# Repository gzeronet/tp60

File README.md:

# TP60

Custom PCB for gh60-like keyboard with trackpoint. Teensy 2.0 as main Controller.

Also see:

https://github.com/gzeronet/teensy-trackpoint-tmk-keyboard/

## PCB View

### Front

### Back

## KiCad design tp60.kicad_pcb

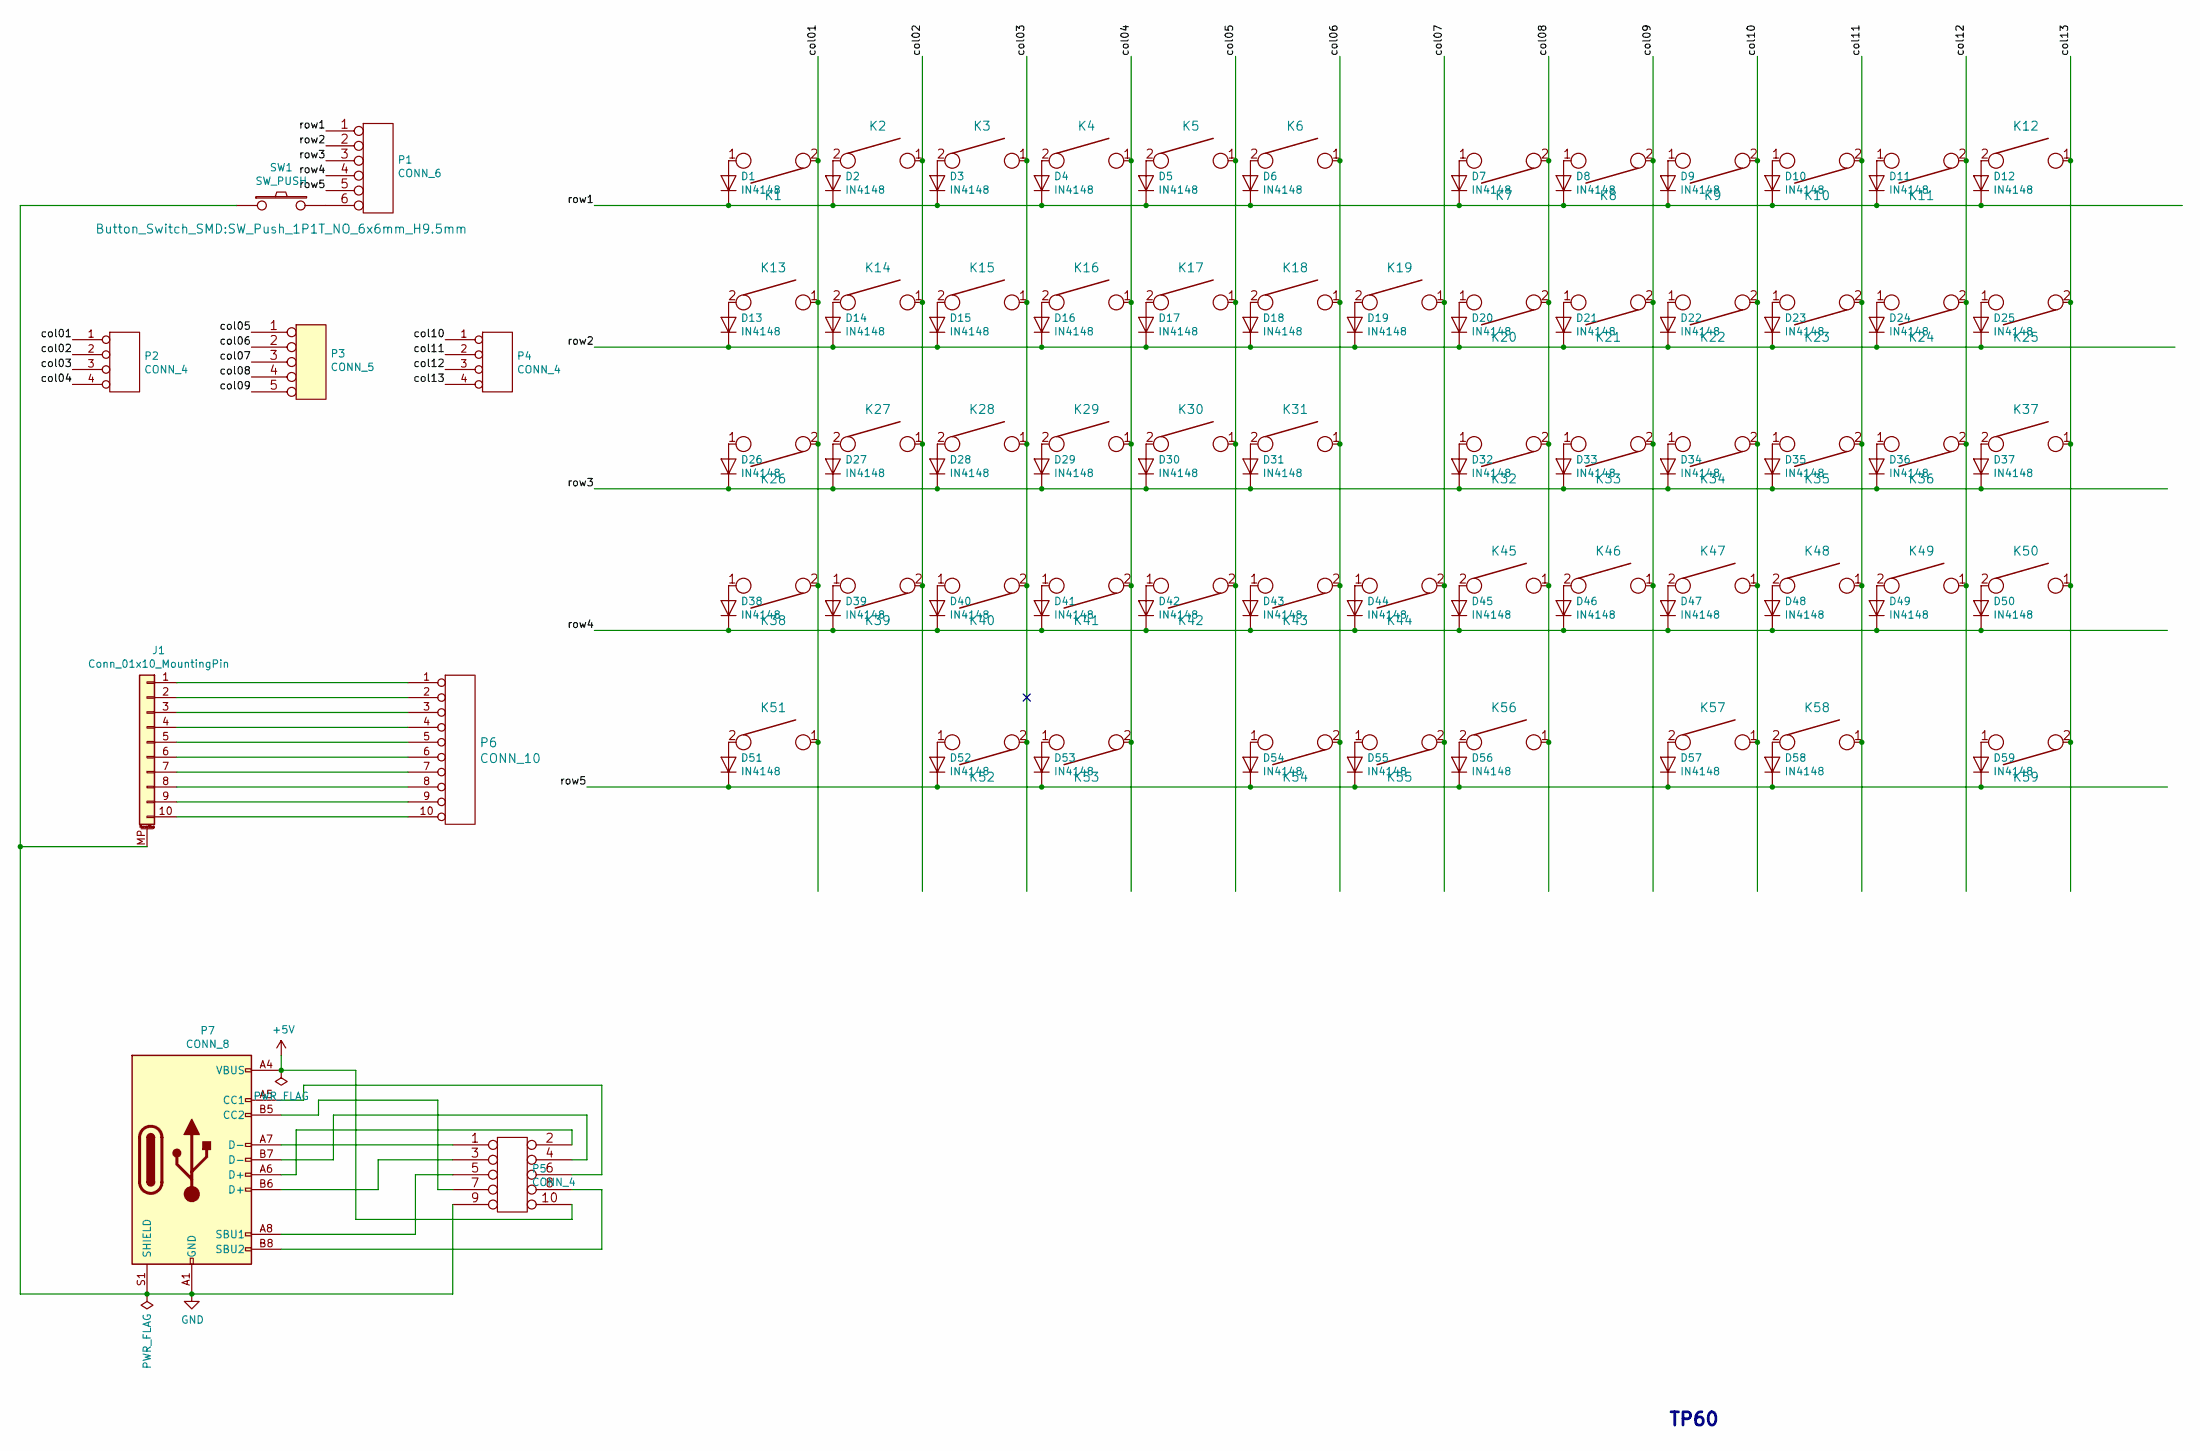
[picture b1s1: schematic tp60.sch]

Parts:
D1, D2, D3, D4, D5, D6, D7, D8, D9, D10, D11, D12, D13, D14, D15, D16, D17, D18, D19, D20, D21, D22, D23, D24, D25, D26, D27, D28, D29, D30, D31, D32, D33, D34, D35, D36, D37, D38, D39, D40, D41, D42, D43, D44, D45, D46, D47, D48, D49, D50, D51, D52, D53, D54, D55, D56, D57, D58, D59: IN4148; D_DO-35_SOD27_P7.62mm_Horizontal
J1: Conn_01x10_MountingPin; TE_1-84952-0_1x10-1MP_P1.0mm_Horizontal
K1, K2, K3, K4, K5, K6, K7, K8, K9, K10, K11, K12, K13, K14, K15, K16, K17, K18, K19, K20, K21, K22, K23, K24, K25, K26, K27, K28, K29, K30, K31, K32, K33, K34, K35, K36, K37, K38, K39, K40, K41, K42, K43, K44, K45, K46, K47, K48, K49, K50, K51, K52, K53, K54, K55, K56, K57, K58, K59: KEYSW; SW_MX_1280
P1: CONN_6; PinHeader_1x06_P2.54mm_Vertical
P2, P4: CONN_4; PinHeader_1x04_P2.54mm_Vertical
P3: CONN_5; PinHeader_1x05_P2.54mm_Vertical
P5: CONN_4; PinHeader_2x05_P2.54mm_Vertical
P6: CONN_10; PinHeader_2x05_P2.54mm_Vertical
P7: CONN_8; HRO-TYPE-C-31-M-12-PIN
SW1: SW_PUSH; SW_Push_1P1T_NO_6x6mm_H9.5mm

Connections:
+5V: P5.10, P7.A4 (VBUS), P7.A9 (VBUS), P7.B4 (VBUS), P7.B9 (VBUS)
/col01: K1.2, K13.1, K26.2, K38.2, K51.1, P2.1
/col02: K2.1, K14.1, K27.1, K39.2, P2.2
/col03: K3.1, K15.1, K28.1, K40.2, K52.2, P2.3
/col04: K4.1, K16.1, K29.1, K41.2, K53.2, P2.4
/col05: K5.1, K17.1, K30.1, K42.2, P3.1
/col06: K6.1, K18.1, K31.1, K43.2, K54.2, P3.2
/col07: K19.1, K44.2, K55.2, P3.3
/col08: K7.2, K20.2, K32.2, K45.1, K56.1, P3.4
/col09: K8.2, K21.2, K33.2, K46.1, P3.5
/col10: K9.2, K22.2, K34.2, K47.1, K57.1, P4.1
/col11: K10.2, K23.2, K35.2, K48.1, K58.1, P4.2
/col12: K11.2, K24.2, K36.2, K49.1, P4.3
/col13: K12.1, K25.2, K37.1, K50.1, K59.2, P4.4
/row1: D1.1 (K), D2.1 (K), D3.1 (K), D4.1 (K), D5.1 (K), D6.1 (K), D7.1 (K), D8.1 (K), D9.1 (K), D10.1 (K), D11.1 (K), D12.1 (K), P1.1
/row2: D13.1 (K), D14.1 (K), D15.1 (K), D16.1 (K), D17.1 (K), D18.1 (K), D19.1 (K), D20.1 (K), D21.1 (K), D22.1 (K), D23.1 (K), D24.1 (K), D25.1 (K), P1.2
/row3: D26.1 (K), D27.1 (K), D28.1 (K), D29.1 (K), D30.1 (K), D31.1 (K), D32.1 (K), D33.1 (K), D34.1 (K), D35.1 (K), D36.1 (K), D37.1 (K), P1.3
/row4: D38.1 (K), D39.1 (K), D40.1 (K), D41.1 (K), D42.1 (K), D43.1 (K), D44.1 (K), D45.1 (K), D46.1 (K), D47.1 (K), D48.1 (K), D49.1 (K), D50.1 (K), P1.4
/row5: D51.1 (K), D52.1 (K), D53.1 (K), D54.1 (K), D55.1 (K), D56.1 (K), D57.1 (K), D58.1 (K), D59.1 (K), P1.5
GND: J1.MP (MountPin), P5.9, P7.A1 (GND), P7.A12 (GND), P7.B1 (GND), P7.B12 (GND), P7.S1 (SHIELD), SW1.1
unnamed: D1.2 (A), K1.1
unnamed: D2.2 (A), K2.2
unnamed: D3.2 (A), K3.2
unnamed: D4.2 (A), K4.2
unnamed: D5.2 (A), K5.2
unnamed: D6.2 (A), K6.2
unnamed: D7.2 (A), K7.1
unnamed: D8.2 (A), K8.1
unnamed: D9.2 (A), K9.1
unnamed: D10.2 (A), K10.1
unnamed: D11.2 (A), K11.1
unnamed: D12.2 (A), K12.2
unnamed: D13.2 (A), K13.2
unnamed: D14.2 (A), K14.2
unnamed: D15.2 (A), K15.2
unnamed: D16.2 (A), K16.2
unnamed: D17.2 (A), K17.2
unnamed: D18.2 (A), K18.2
unnamed: D19.2 (A), K19.2
unnamed: D20.2 (A), K20.1
unnamed: D21.2 (A), K21.1
unnamed: D22.2 (A), K22.1
unnamed: D23.2 (A), K23.1
unnamed: D24.2 (A), K24.1
unnamed: D25.2 (A), K25.1
unnamed: D26.2 (A), K26.1
unnamed: D27.2 (A), K27.2
unnamed: D28.2 (A), K28.2
unnamed: D29.2 (A), K29.2
unnamed: D30.2 (A), K30.2
unnamed: D31.2 (A), K31.2
unnamed: D32.2 (A), K32.1
unnamed: D33.2 (A), K33.1
unnamed: D34.2 (A), K34.1
unnamed: D35.2 (A), K35.1
unnamed: D36.2 (A), K36.1
unnamed: D37.2 (A), K37.2
unnamed: D38.2 (A), K38.1
unnamed: D39.2 (A), K39.1
unnamed: D40.2 (A), K40.1
unnamed: D41.2 (A), K41.1
unnamed: D42.2 (A), K42.1
unnamed: D43.2 (A), K43.1
unnamed: D44.2 (A), K44.1
unnamed: D45.2 (A), K45.2
unnamed: D46.2 (A), K46.2
unnamed: D47.2 (A), K47.2
unnamed: D48.2 (A), K48.2
unnamed: D49.2 (A), K49.2
unnamed: D50.2 (A), K50.2
unnamed: D51.2 (A), K51.2
unnamed: D52.2 (A), K52.1
unnamed: D53.2 (A), K53.1
unnamed: D54.2 (A), K54.1
unnamed: D55.2 (A), K55.1
unnamed: D56.2 (A), K56.2
unnamed: D57.2 (A), K57.2
unnamed: D58.2 (A), K58.2
unnamed: D59.2 (A), K59.1
unnamed: J1.1, P6.1
unnamed: J1.2, P6.2
unnamed: J1.3, P6.3
unnamed: J1.4, P6.4
unnamed: J1.5, P6.5
unnamed: J1.6, P6.6
unnamed: J1.7, P6.7
unnamed: J1.8, P6.8
unnamed: J1.9, P6.9
unnamed: J1.10, P6.10
unnamed: P1.6, SW1.2
unnamed: P5.1, P7.A7 (D-)
unnamed: P5.2, P7.A6 (D+)
unnamed: P5.3, P7.B6 (D+)
unnamed: P5.4, P7.B7 (D-)
unnamed: P5.5, P7.A8 (SBU1)
unnamed: P5.6, P7.A5 (CC1)
unnamed: P5.7, P7.B5 (CC2)
unnamed: P5.8, P7.B8 (SBU2)

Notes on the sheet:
TP60

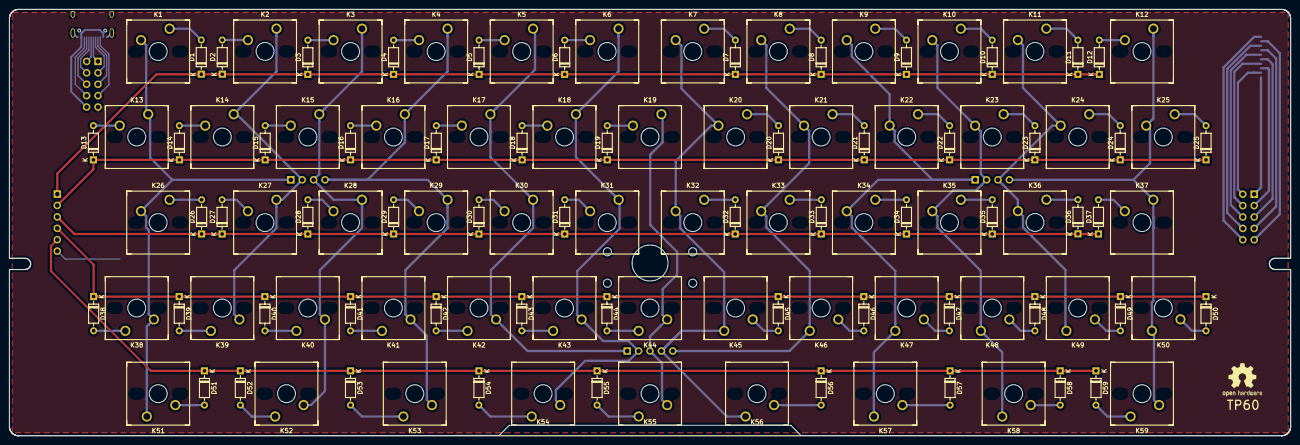
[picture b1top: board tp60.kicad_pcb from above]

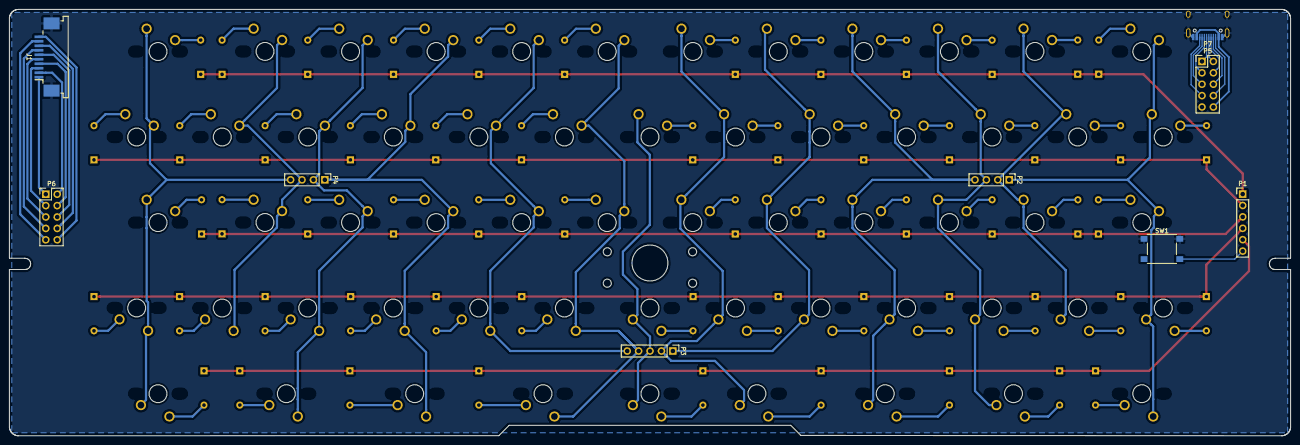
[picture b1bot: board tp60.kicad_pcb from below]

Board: 2 copper layers, 285.3 x 94.9 mm, 127 parts (9 on the bottom side), 98 nets.

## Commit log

2020-05-03 init repo
2020-05-03 refilled zone
2020-09-08 rewrite pcb
2020-09-11 improved pcb lines
2020-09-11 made up pcb img and README
2020-09-12 typo fixed
2020-09-16 Update README.md
    display pcb img
2020-10-03 adjusted socket pos
